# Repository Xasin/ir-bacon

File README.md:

# ir-bacon
Small, multi-purpose IR Beacon disks with LEDs, buzzers, buttons!

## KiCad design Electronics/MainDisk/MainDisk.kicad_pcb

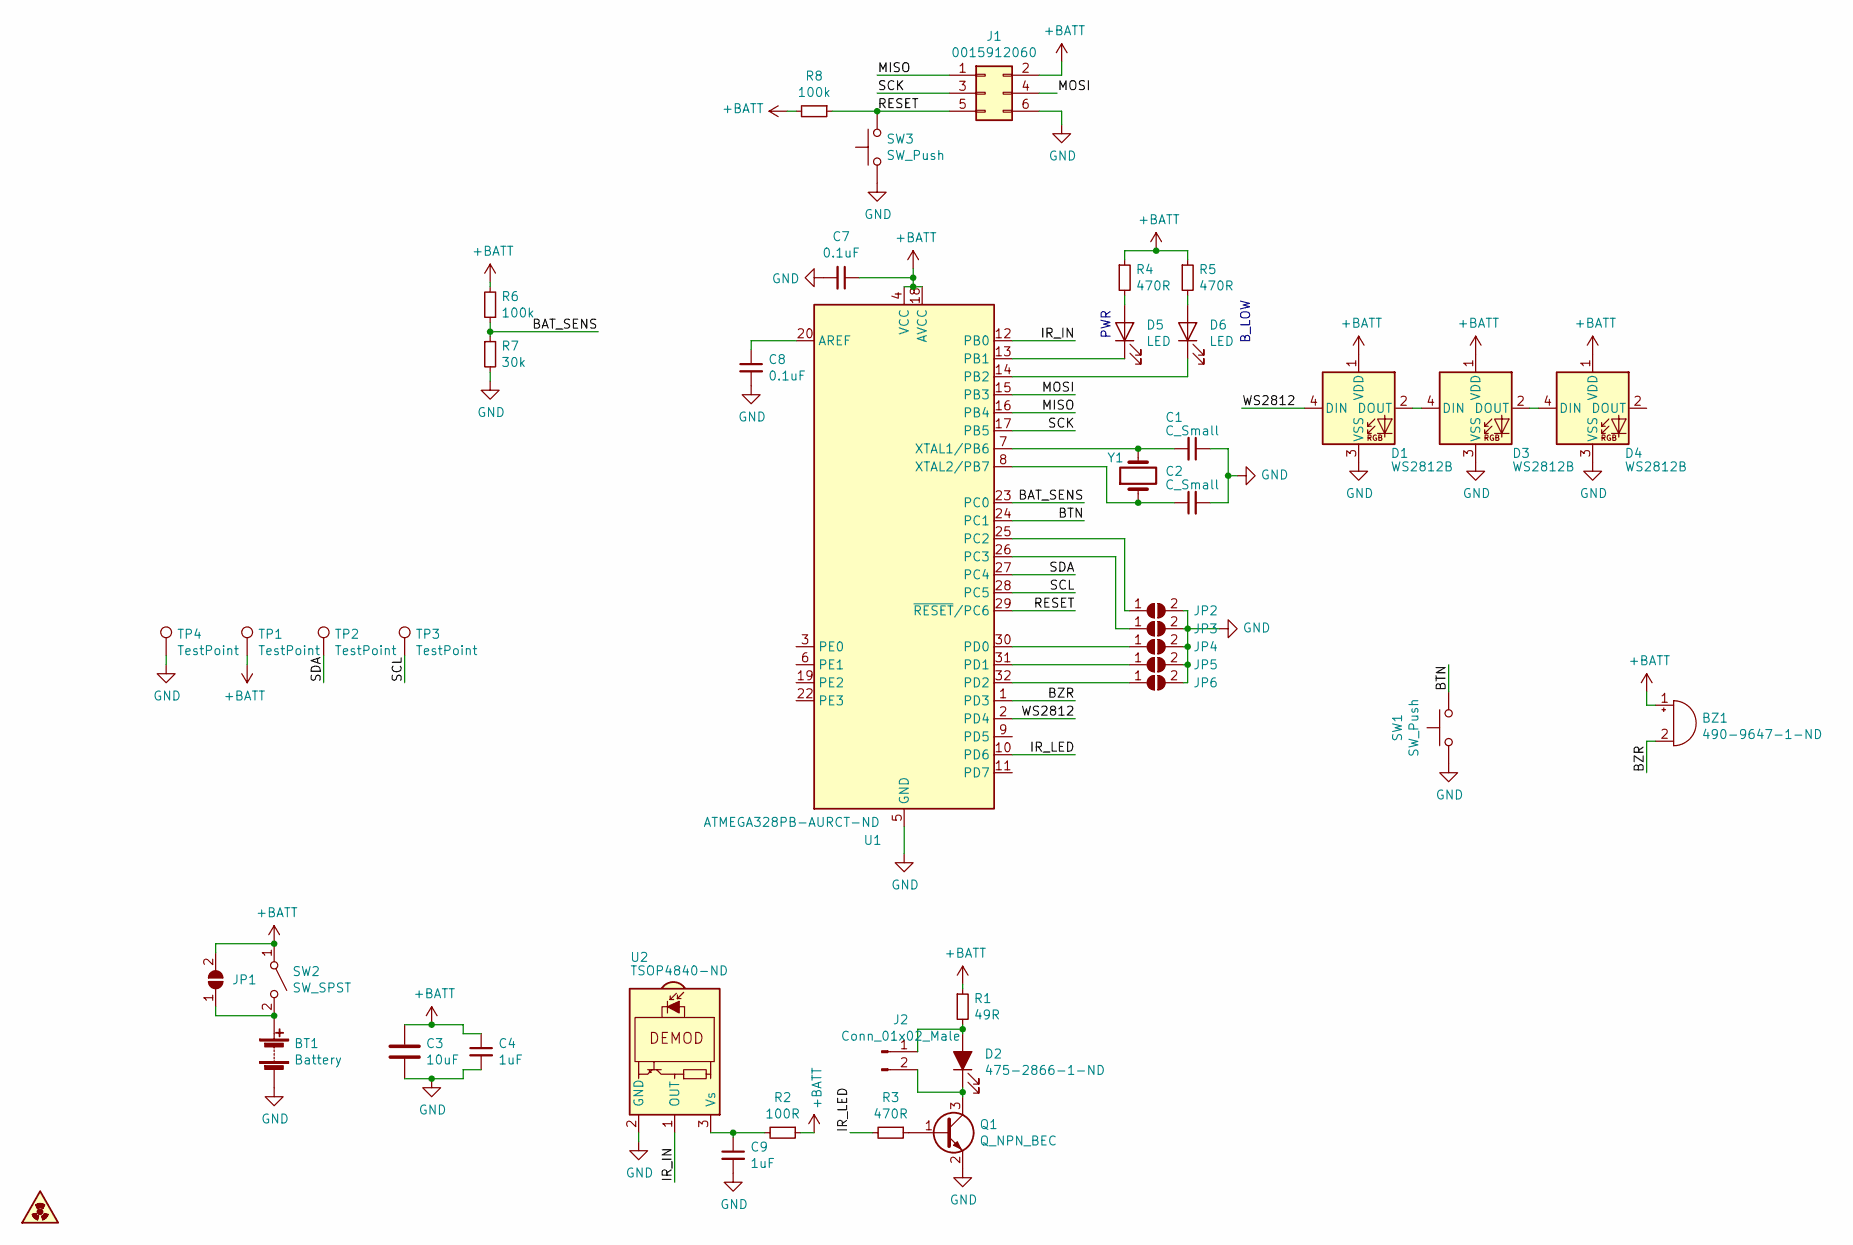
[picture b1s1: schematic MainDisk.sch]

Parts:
BT1: Battery; JST_PH_B2B-PH-K_1x02_P2.00mm_Vertical
BZ1: 490-9647-1-ND; Buzzer_Murata_PKMCS0909E4000-R1
C1, C2: C_Small; C_0805_2012Metric
C3: 10uF; C_0805_2012Metric
C4, C9: 1uF; C_0805_2012Metric
C7, C8: 0.1uF; C_0805_2012Metric
D1, D3, D4: WS2812B; LED_WS2812B_PLCC4_5.0x5.0mm_P3.2mm
D2: 475-2866-1-ND; LED_PLCC-2
D5, D6: LED; LED_0805_2012Metric
J1: 0015912060; PinHeader_2x03_P2.54mm_Vertical_SMD
J2: Conn_01x02_Male; PinHeader_1x02_P2.00mm_Vertical
JP1: SolderJumper_2_Open; SolderJumper-2_P1.3mm_Open_TrianglePad1.0x1.5mm
JP2, JP3, JP4, JP5, JP6: SolderJumper_2_Open; SolderJumper-2_P1.3mm_Open_RoundedPad1.0x1.5mm
Q1: Q_NPN_BEC; SOT-23
R1: 49R; R_0805_2012Metric
R2: 100R; R_0805_2012Metric
R3, R4, R5: 470R; R_0805_2012Metric
R6, R8: 100k; R_0805_2012Metric
R7: 30k; R_0805_2012Metric
SW1: SW_Push; SW_SPST_PTS645
SW2: SW_SPST; PinHeader_1x02_P2.00mm_Vertical
SW3: SW_Push; SW_SPST_B3U-1000P
SYM1: SYM_Radioactive_Radiation_Small; Logo
TP1, TP2, TP3, TP4: TestPoint; TestPoint_Keystone_5019_Minature
U1: ATMEGA328PB-AURCT-ND; TQFP-32_7x7mm_P0.8mm
U2: TSOP4840-ND; Vishay_MOLD-3Pin
Y1: 535-10212-1-ND; Crystal_SMD_HC49-SD

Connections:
+BATT: BZ1.1 (-), C3.1, C4.1, C7.1, D1.1 (VDD), D3.1 (VDD), D4.1 (VDD), J1.2, JP1.2 (B), R1.1, R2.1, R4.1, R5.1, R6.2, R8.2, SW2.1 (A), TP1.1, U1.4 (VCC), U1.18 (AVCC)
/BAT_SENS: R6.1, R7.1, U1.23 (PC0)
/BTN: SW1.2, U1.24 (PC1)
/BZR: BZ1.2 (+), U1.1 (PD3)
/IR_IN: U1.12 (PB0), U2.1 (OUT)
/IR_LED: R3.2, U1.10 (PD6)
/MISO: J1.1, U1.16 (PB4)
/MOSI: J1.4, U1.15 (PB3)
/RESET: J1.5, R8.1, SW3.2, U1.29 (~RESET~/PC6)
/SCK: J1.3, U1.17 (PB5)
/SCL: TP3.1, U1.28 (PC5)
/SDA: TP2.1, U1.27 (PC4)
/WS2812: D1.4 (DIN), U1.2 (PD4)
GND: BT1.2 (-), C1.1, C2.2, C3.2, C4.2, C7.2, C8.2, C9.2, D1.3 (VSS), D3.3 (VSS), D4.3 (VSS), J1.6, JP2.2 (B), JP3.2 (B), JP4.2 (B), JP5.2 (B), JP6.2 (B), Q1.2 (E), R7.2, SW1.1, SW3.1, TP4.1, U1.5 (GND), U1.21 (GND), U2.2 (GND)
unnamed: BT1.1 (+), JP1.1 (A), SW2.2 (B)
unnamed: C1.2, U1.7 (XTAL1/PB6), Y1.2
unnamed: C2.1, U1.8 (XTAL2/PB7), Y1.1
unnamed: C8.1, U1.20 (AREF)
unnamed: C9.1, R2.2, U2.3 (Vs)
unnamed: D1.2 (DOUT), D3.4 (DIN)
unnamed: D2.1 (K), J2.2, Q1.3 (C)
unnamed: D2.2 (A), J2.1, R1.2
unnamed: D3.2 (DOUT), D4.4 (DIN)
unnamed: D5.1 (K), U1.13 (PB1)
unnamed: D5.2 (A), R4.2
unnamed: D6.1 (K), U1.14 (PB2)
unnamed: D6.2 (A), R5.2
unnamed: JP2.1 (A), U1.25 (PC2)
unnamed: JP3.1 (A), U1.26 (PC3)
unnamed: JP4.1 (A), U1.30 (PD0)
unnamed: JP5.1 (A), U1.31 (PD1)
unnamed: JP6.1 (A), U1.32 (PD2)
unnamed: Q1.1 (B), R3.1

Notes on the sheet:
PWR
B_LOW

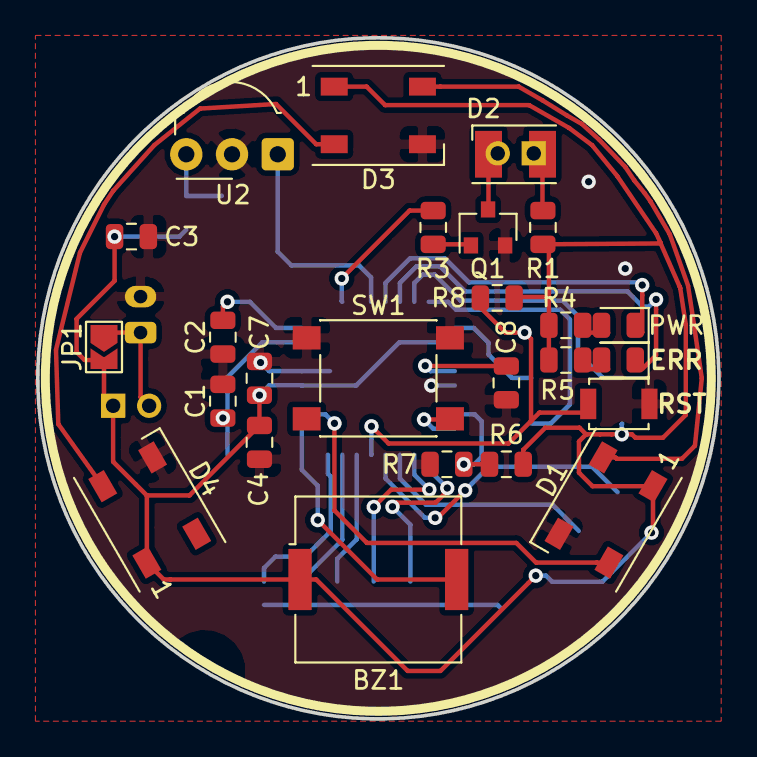
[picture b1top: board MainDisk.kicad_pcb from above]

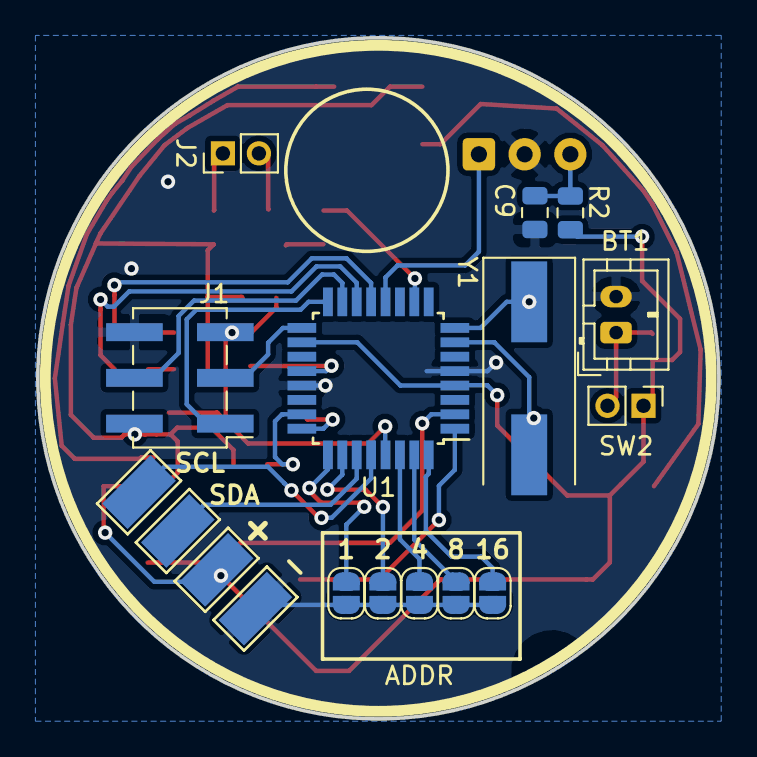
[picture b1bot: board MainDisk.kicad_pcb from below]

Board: 2 copper layers, 37.8 x 37.8 mm, 43 parts (18 on the bottom side), 33 nets.

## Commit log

2019-05-19 Began working on the disk
2019-05-21 Continued work on the Disk
2019-05-21 More smol tweaks to the bacon
2019-05-21 More or less Rev. 1
2019-05-22 Began working on code
2019-05-22 Small changes to PCB
2019-05-22 Finally got things working
2019-05-23 Began working on COLOR
2019-05-24 Added a few more modes
2019-05-27 Began working on fancy and easy light handling!
2019-05-28 Added beepboops
2019-06-03 Polished WS2812 and IR interaction
2022-01-08 Add changes to KiCAD PCB
